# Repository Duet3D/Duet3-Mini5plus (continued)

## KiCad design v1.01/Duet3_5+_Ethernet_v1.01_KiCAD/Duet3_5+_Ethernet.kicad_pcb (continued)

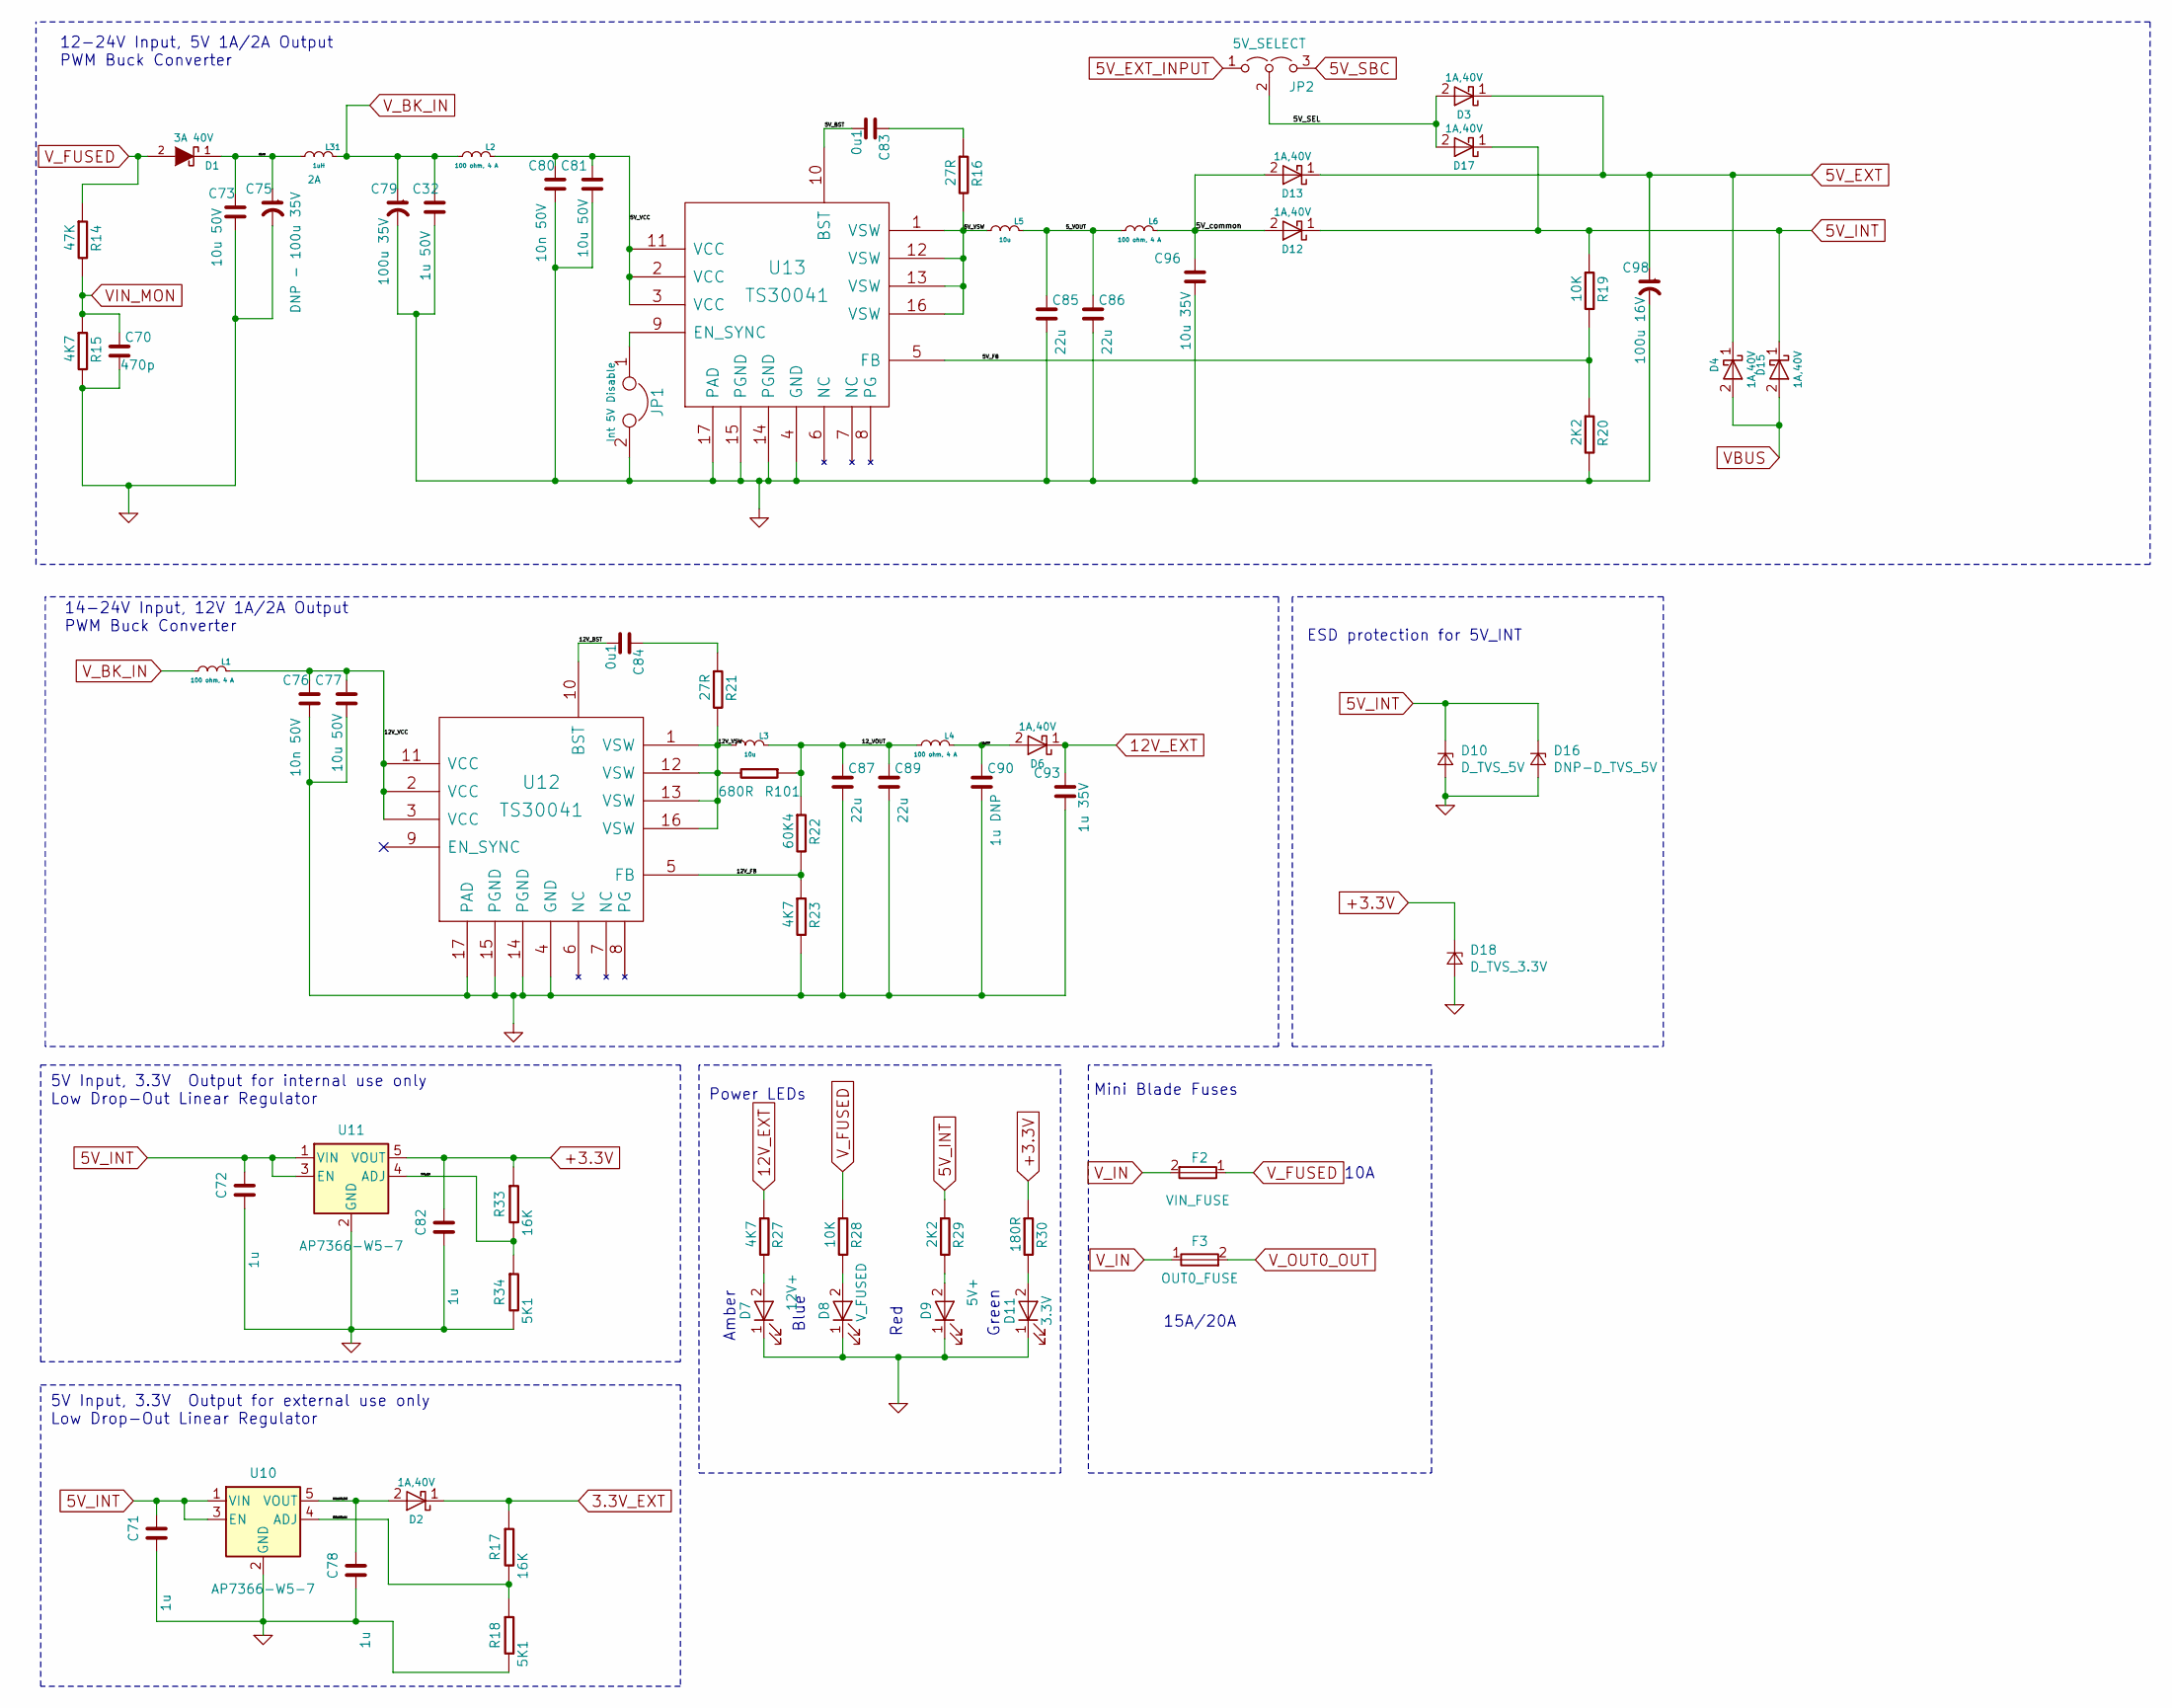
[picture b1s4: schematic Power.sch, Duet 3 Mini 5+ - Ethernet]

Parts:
C32: 1u 50V; C_0603_1608Metric_Wbry; Part Number CL10A105KB8NNNC
C70: 470p; C_0402_1005Metric_Wbry; Part Number CC0402KRX7R9BB471 or similar 10V+
C71, C72, C78, C82: 1u; C_0603_1608Metric_Wbry; Part Number CL10B105MO8NNWC or equivalent 16V+
C73, C77, C81: 10u 50V; C_1206_3216Metric; Part Number CL31A106MBHNNNE
C75: DNP - 100u 35V; CP_Elec_6.3x7.7; Part Number DNP e.g EEEFT1V101AP or 865080545012
C76: 10n 50V; C_0603_1608Metric_Wbry; Part Number CL10B103KB8NNNC
C79: 100u 35V; CP_Elec_6.3x7.7; Part Number e.g EEEFT1V101AP or 865080545012
C80: 10n 50V; C_0603_1608Metric_Wbry; Part Number CL10B103KB8NNNC or similar
C83, C84: 0u1; C_0402_1005Metric_Wbry; Part Number CL05A104KA5NNNC or similar
C85, C86, C87, C89: 22u; C_0805_2012Metric; Rating 25V; Part Number GRM21BR61E226ME44L
C90: 1u DNP; C_0603_1608Metric_Wbry; Rating 35V + DNP; Part Number CL10A105KB8NNNC or equivalent
C93: 1u 35V; C_0603_1608Metric_Wbry; Rating 35V +; Part Number CL10A105KB8NNNC or equivalent 35V+
C96: 10u 35V; C_1206_3216Metric; Part Number CL31A106KBHNNNE or similar 35V+
C98: 100u 16V; CP_Elec_6.3x7.7; Part Number 865080545012 or similar 16V+
D1: 3A 40V; D_SMA; Part Number ACDBA340-HF, SK34ATR or similar
D2, D3, D4, D6, D12, D13, D15, D17: 1A,40V; D_SOD-123F; Rating 1A,40V; Part Number DSS14UTR or RB162MM-40TR or similar
D7: 12V+; LED_0603_1608Metric; Part Number 150060AS75000 or equivalent Amber
D8: V_FUSED; LED_0603_1608Metric; Part Number 150060BS75000 or equivalent Blue
D9: 5V+; LED_0603_1608Metric; Part Number 150060RS75000 or equivalent Red
D10: D_TVS_5V; DFN1610-2L; Part Number 824032815 or 824031815 (DNP if D16 is p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
D11: 3.3V; LED_0603_1608Metric; Part Number 150060VS75000 or equivalent Green
D16: DNP-D_TVS_5V; D_SMC; Part Number SMCJ5.0A (DNP if D10 is populated)
D18: D_TVS_3.3V; DFN1610-2L; Part Number 824032813
F2: VIN_FUSE; MCCQ-122-minibladefuseholder; Part Number MCCQ-122 + 10A fuse
F3: OUT0_FUSE; MCCQ-122-minibladefuseholder; Part Number MCCQ-122 +15A fuse
JP1: Int 5V Disable; PinHeader_1x02_P2.54mm_Vertical; Part Number THS-02-R
JP2: 5V_SELECT; PinHeader_1x03_P2.54mm_Vertical; Part Number THS-03-R
L1, L2, L4, L6: 100 ohm, 4 A; L_0805_2012Metric; Part Number MPZ2012S101A or similar
L3, L5: 10u; L_Wuerth_7440405xxxx; Part Number 74404054100 or NR5040T100M
L31: 1uH; L_0806_2016Metric; Rating 2A; Part Number BDCD002016101R0MS1 or MAKK2016T1R0M
R14: 47K; R_0402_1005Metric_Wbry; Part Number RMCF0402FT47K0
R15, R23, R27: 4K7; R_0402_1005Metric_Wbry; Part Number RK73H1ETTP4701F
R16, R21: 27R; R_0402_1005Metric_Wbry; Rating 0.1W+; Part Number RK73H1ETTP10R0F
R17, R33: 16K; R_0402_1005Metric_Wbry; Part Number RMCF0402FT16K0
R18, R34: 5K1; R_0402_1005Metric_Wbry; Part Number ERJ3EKF5101V
R19, R28: 10K; R_0402_1005Metric_Wbry; Part Number RK73H1ETTP1002F
R20, R29: 2K2; R_0402_1005Metric_Wbry; Part Number RK73H1ETTP2201F
R22: 60K4; R_0402_1005Metric_Wbry; Part Number ERJ-2RKF6042X
R30: 180R; R_0402_1005Metric_Wbry; Part Number RMCF0402FT180R
R101: 680R; R_0805_2012Metric; Rating 0.5W; Part Number 680R 0.5W (ERJ-P06F6653V 665R is an alt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
U10, U11: AP7366-W5-7; SOT-23-5; Part Number AP7366-W5-7
U12, U13: TS30041; QFN-16-1EP_3x3mm_P0.5mm_EP1.8x1.8mm_ThermalVias; Part Number TS30041-M000QFNR

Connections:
3.3V_EXT: D2.1 (K), R17.1; also elsewhere on the board
5V_EXT: C98.1, D3.1 (K), D4.1 (K), D13.1 (K); also elsewhere on the board
5V_EXT_INPUT: JP2.1 (A); also elsewhere on the board
5V_INT: C71.1, C72.1, D10.1 (K), D12.1 (K), D15.1 (K), D16.1 (K), D17.1 (K), R19.1, R29.1, U10.1 (VIN), U10.3 (EN), U11.1 (VIN), U11.3 (EN); also elsewhere on the board
5V_SBC: JP2.3 (B); also elsewhere on the board
12V_EXT: C93.1, D6.1 (K), R27.1; also elsewhere on the board
+3.3V: C82.1, D18.1 (K), R30.1, R33.1, U11.5 (VOUT); also elsewhere on the board
/Power/3V3_ADJ: R33.2, R34.1, U11.4 (ADJ)
/Power/3V3_EXT_ADJ: R17.2, R18.1, U10.4 (ADJ)
/Power/3V3_EXT_OUT: C78.1, D2.2 (A), U10.5 (VOUT)
/Power/5V_BST: C83.2, U13.10 (BST)
/Power/5V_FB: R19.2, R20.1, U13.5 (FB)
/Power/5V_SEL: D3.2 (A), D17.2 (A), JP2.2 (C)
/Power/5V_VCC: C80.1, C81.1, L2.1 (A), U13.2 (VCC), U13.3 (VCC), U13.11 (VCC)
/Power/5V_VSW: L5.2 (B), R16.2, U13.1 (VSW), U13.12 (VSW), U13.13 (VSW), U13.16 (VSW)
/Power/5V_common: C96.1, D12.2 (A), D13.2 (A), L6.1 (A)
/Power/5_VOUT: C85.1, C86.1, L5.1 (A), L6.2 (B)
/Power/12V_BST: C84.2, U12.10 (BST)
/Power/12V_FB: R22.2, R23.1, U12.5 (FB)
/Power/12V_VCC: C76.1, C77.1, L1.1 (A), U12.2 (VCC), U12.3 (VCC), U12.11 (VCC)
/Power/12V_VSW: L3.2 (B), R21.2, R101.2, U12.1 (VSW), U12.12 (VSW), U12.13 (VSW), U12.16 (VSW)
/Power/12_VOUT: C87.1, C89.1, L3.1 (A), L4.2 (B), R22.1, R101.1
/Power/L4_OUT: C90.1, D6.2 (A), L4.1 (A)
/Power/d1out: C73.1, C75.1, D1.1 (K), L31.2 (B)
GND: C32.2, C70.2, C71.2, C72.2, C73.2, C75.2, C76.2, C77.2, C78.2, C79.2, C80.2, C81.2, C82.2, C85.2, C86.2, C87.2, C89.2, C90.2, C93.2, C96.2, C98.2, D7.1 (K), D8.1 (K), D9.1 (K), D10.2 (A), D11.1 (K), D16.2 (A), D18.2 (A), JP1.2, R15.2, R18.2, R20.2, R23.2, R34.2, U10.2 (GND), U11.2 (GND), U12.4 (GND), U12.14 (PGND), U12.15 (PGND), U12.17 (PAD), U13.4 (GND), U13.14 (PGND), U13.15 (PGND), U13.17 (PAD); also elsewhere on the board
unnamed: C83.1, R16.1
unnamed: C84.1, R21.1
unnamed: D7.2 (A), R27.2
unnamed: D8.2 (A), R28.2
unnamed: D9.2 (A), R29.2
unnamed: D11.2 (A), R30.2
unnamed: JP1.1, U13.9 (EN_SYNC)
VBUS: D4.2 (A), D15.2 (A); also elsewhere on the board
VIN_MON: C70.1, R14.2, R15.1; also elsewhere on the board
V_BK_IN: C32.1, C79.1, L1.2 (B), L2.2 (B), L31.1 (A)
V_FUSED: D1.2 (A), F2.1, R14.1, R28.1; also elsewhere on the board
V_IN: F2.2, F3.1; also elsewhere on the board
V_OUT0_OUT: F3.2; also elsewhere on the board

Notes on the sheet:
Mini Blade Fuses
5V Input, 3.3V Output for internal use only Low Drop-Out Linear Regulator
Power LEDs
Blue
Red
Green
10A
15A/20A
5V Input, 3.3V Output for external use only Low Drop-Out Linear Regulator
14-24V Input, 12V 1A/2A Output PWM Buck Converter
Amber
ESD protection for 5V_INT
12-24V Input, 5V 1A/2A Output PWM Buck Converter

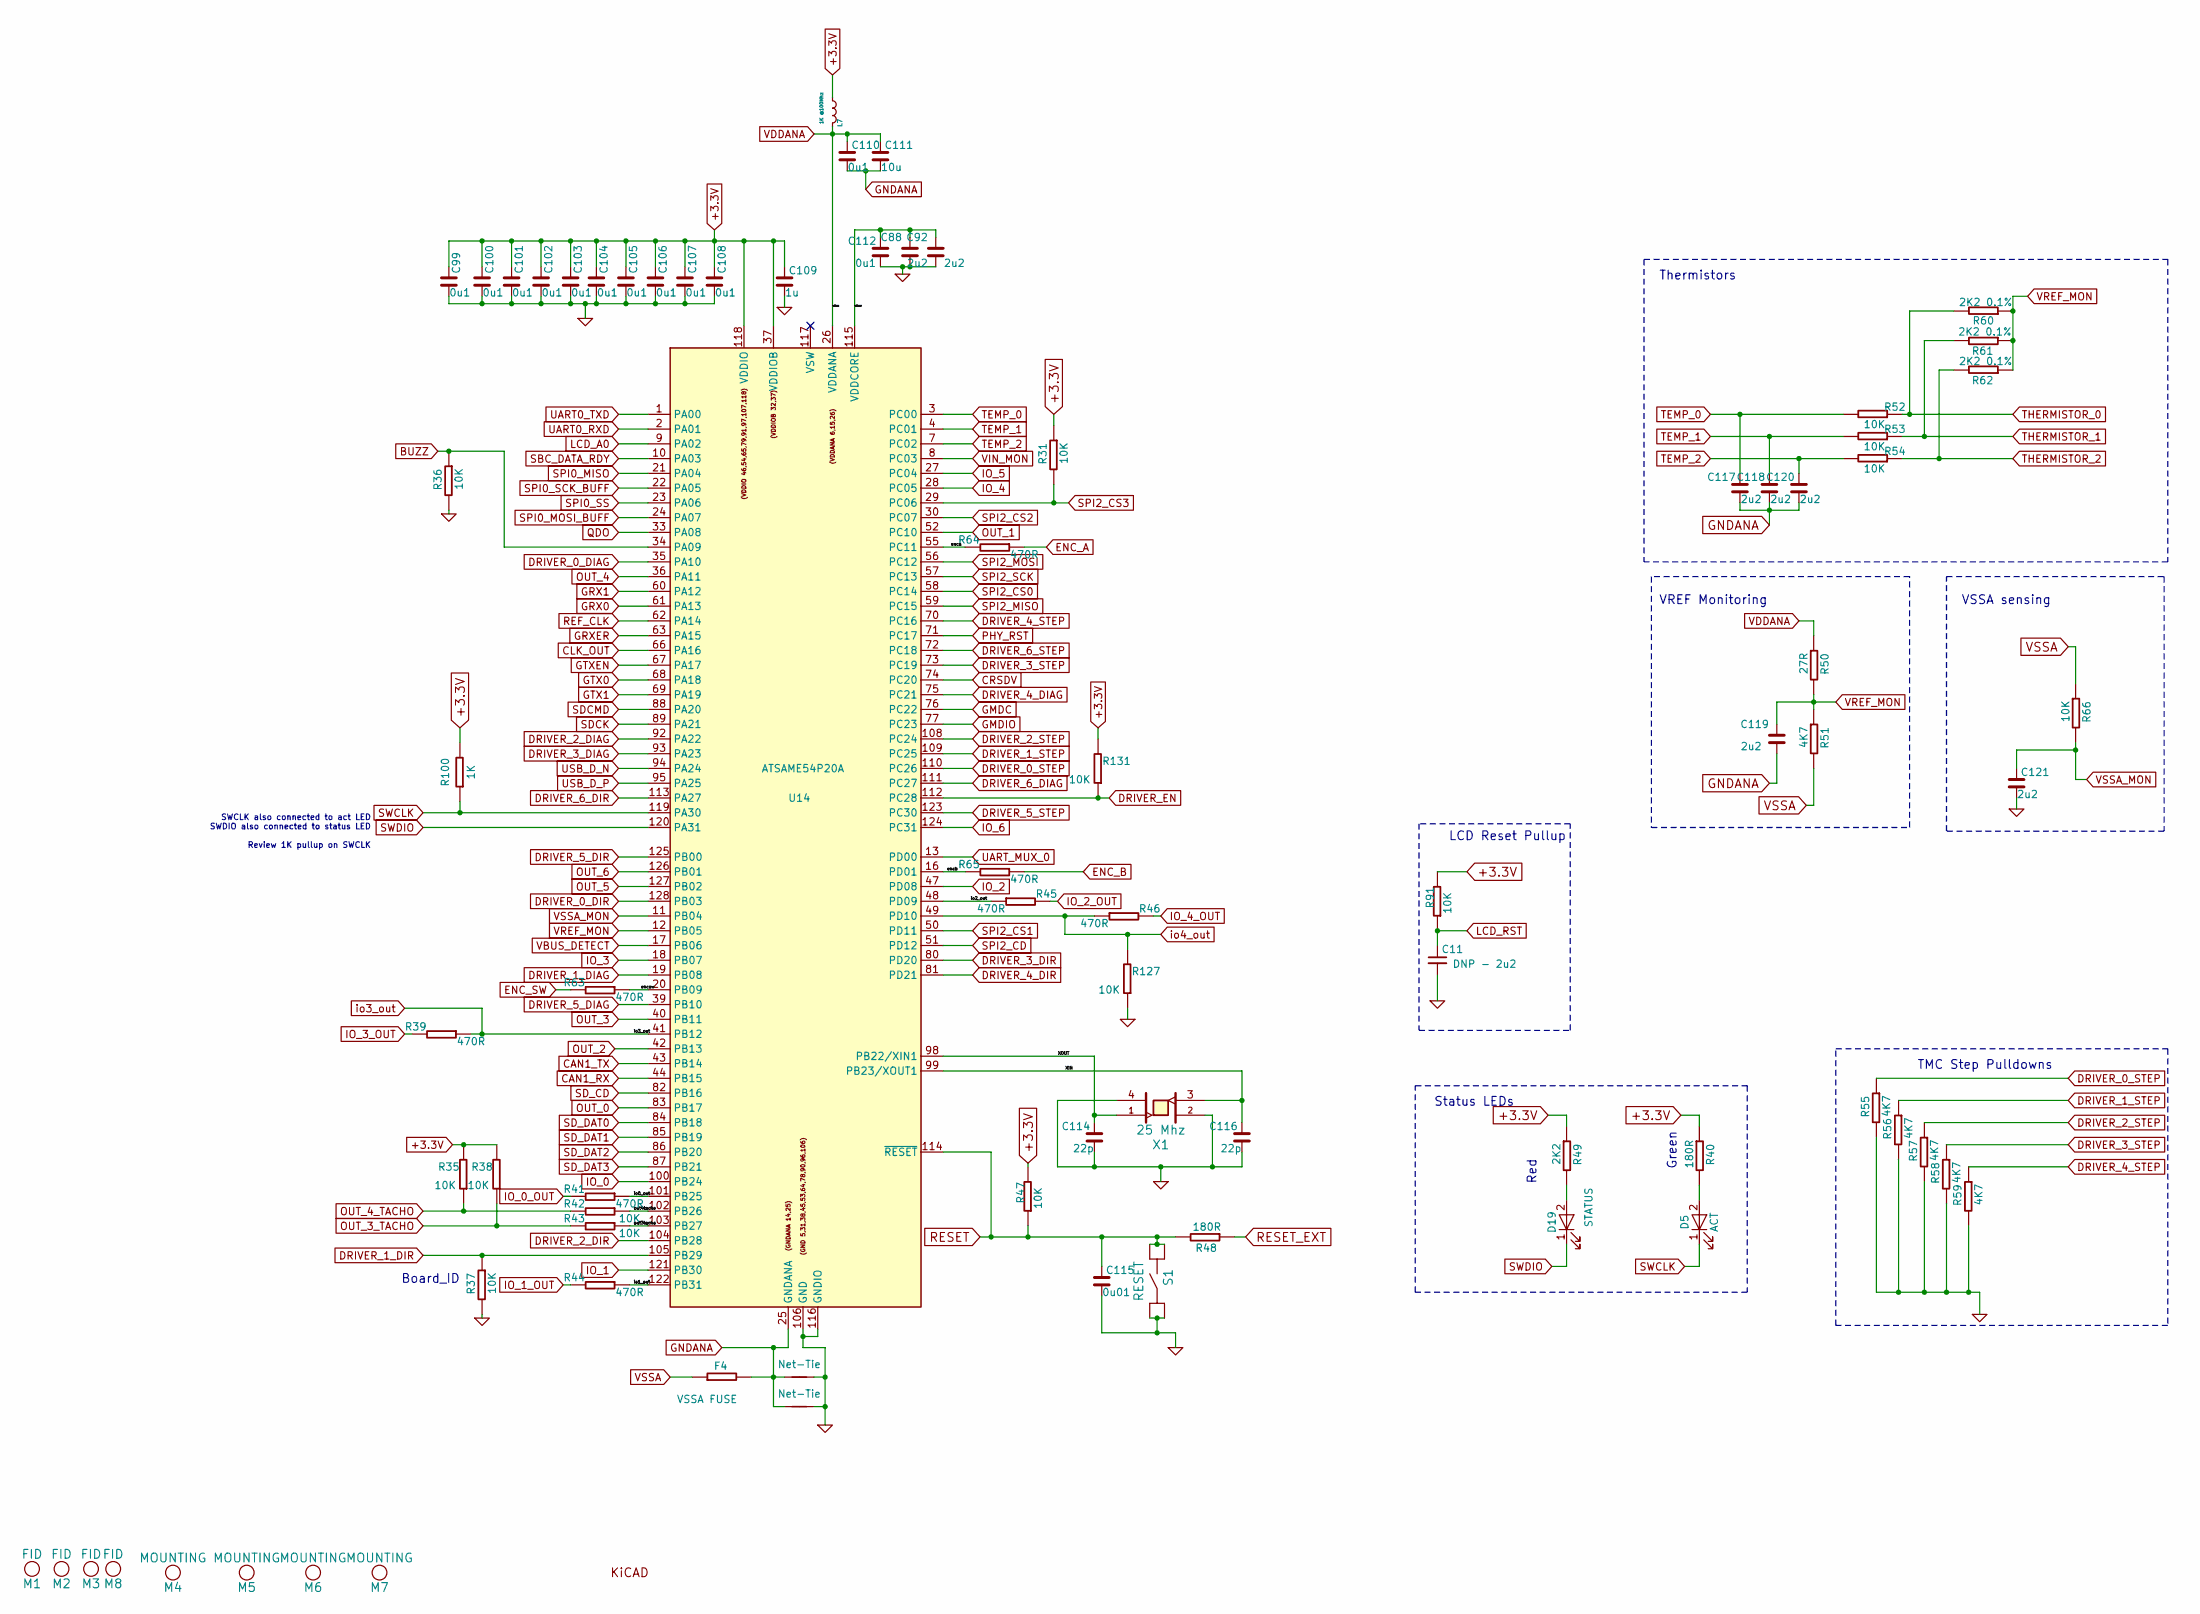
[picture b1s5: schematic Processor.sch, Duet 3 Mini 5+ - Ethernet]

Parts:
C11: DNP - 2u2; C_0402_1005Metric_Wbry; Part Number DNP - LMK105BJ225KV-F or similar 10v+
C88, C92, C117, C118, C119, C120, C121: 2u2; C_0402_1005Metric_Wbry; Part Number LMK105BJ225KV-F or similar 10v+
C99, C100, C101, C102, C103, C104, C105, C106, C107, C108, C110, C112: 0u1; C_0402_1005Metric_Wbry; Part Number CL05A104KA5NNNC or similar
C109: 1u; C_0603_1608Metric_Wbry; Part Number CL10B105MO8NNWC or equivalent 16V+
C111: 10u; C_0805_2012Metric; Part Number e.g CL21A106KQCLRNC
C114, C116: 22p; C_0402_1005Metric_Wbry; Part Number C0402C220J4GACTU
C115: 0u01; C_0402_1005Metric_Wbry; Part Number TMK105B7103KV-F
D5: ACT; LED_0603_1608Metric; Part Number 150060VS75000 or equivalent Green
D19: STATUS; LED_0603_1608Metric; Part Number 150060RS75000 or equivalent Red
F4: VSSA FUSE; Fuse_1206_3216Metric; Part Number 0ZCJ0020FF2E
L7: 1K @100Mhz; L_0603_1608Metric; Part Number BK1608HS102-T or PE-0603FB102ST or simi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
M1, M2, M3, M8: FID; Fiducial_1mm_Mask2mm; Part Number DNP - Virtual component
M4, M5, M6, M7: MOUNTING; MountingHole_4.3mm_M4; Part Number DNP - Virtual component
M12: Logo_KICAD; KiCad-Logo_6mm_SilkScreen; Part Number DNP - Virtual component
NT1, NT2: Net-Tie; NetTie-2_SMD_Pad0.5mm; Part Number DNP - Virtual component
R31, R35, R36, R37, R38, R42, R43, R47, R52, R53, R54, R66, R91, R127, R131: 10K; R_0402_1005Metric_Wbry; Part Number RK73H1ETTP1002F
R39, R41, R44, R45, R46, R63, R64, R65: 470R; R_0402_1005Metric_Wbry; Part Number RK73H1ETTP4700F
R40, R48: 180R; R_0402_1005Metric_Wbry; Part Number RMCF0402FT180R
R49: 2K2; R_0402_1005Metric_Wbry; Part Number RK73H1ETTP2201F
R50: 27R; R_0402_1005Metric_Wbry; Part Number RC0402FR-0727RL
R51, R55, R56, R57, R58, R59: 4K7; R_0402_1005Metric_Wbry; Part Number RK73H1ETTP4701F
R60, R61, R62: 2K2 0.1%; R_0402_1005Metric_Wbry; Part Number RT0402BRE072K2L
R100: 1K; R_0402_1005Metric_Wbry; Part Number RK73H1ETTP1001F
S1: RESET; SW_SIDE_1_lugs; Part Number LY-A03-02A
U14: ATSAME54P20A; TQFP-128_14x14mm_P0.4mm; Part Number ATSAME54P20A
X1: TSX-3225 25.0000MF10P; Crystal_SMD_ECS-33B-4Pin_3.2x2.5mm; Part Number TSX-3225 25.0000MF10P

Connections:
+3.3V: C99.1, C100.1, C101.1, C102.1, C103.1, C104.1, C105.1, C106.1, C107.1, C108.1, C109.1, L7.2 (B), R31.1, R35.2, R38.2, R40.1, R47.2, R49.1, R91.2, R100.2, R131.2, U14.32 (VDDIOB), U14.37 (VDDIOB), U14.46 (VDDIO), U14.54 (VDDIO), U14.65 (VDDIO), U14.79 (VDDIO), U14.91 (VDDIO), U14.97 (VDDIO), U14.107 (VDDIO), U14.118 (VDDIO); also elsewhere on the board
/Processor/XIN: C116.1, U14.99 (PB23/XOUT1), X1.3
/Processor/XOUT: C114.1, U14.98 (PB22/XIN1), X1.1
/Processor/enca: R64.2, U14.55 (PC11)
/Processor/encb: R65.2, U14.16 (PD01)
/Processor/encsw: R63.1, U14.20 (PB09)
/Processor/io0_out: R41.1, U14.101 (PB25)
/Processor/io1_out: R44.1, U14.122 (PB31)
/Processor/io2_out: R45.1, U14.48 (PD09)
/Processor/out3tacho: R43.1, U14.103 (PB27)
/Processor/out4tacho: R42.1, U14.102 (PB26)
/Processor/vddcore: C88.1, C92.1, C112.1, U14.115 (VDDCORE)
BUZZ: R36.1, U14.34 (PA09); also elsewhere on the board
CAN1_RX: U14.44 (PB15); also elsewhere on the board
CAN1_TX: U14.43 (PB14); also elsewhere on the board
CLK_OUT: U14.66 (PA16); also elsewhere on the board
CRSDV: U14.74 (PC20); also elsewhere on the board
DRIVER_0_DIAG: U14.35 (PA10); also elsewhere on the board
DRIVER_0_DIR: U14.128 (PB03); also elsewhere on the board
DRIVER_0_STEP: R55.1, U14.110 (PC26); also elsewhere on the board
DRIVER_1_DIAG: U14.19 (PB08); also elsewhere on the board
DRIVER_1_DIR: R37.1, U14.105 (PB29); also elsewhere on the board
DRIVER_1_STEP: R56.1, U14.109 (PC25); also elsewhere on the board
DRIVER_2_DIAG: U14.92 (PA22); also elsewhere on the board
DRIVER_2_DIR: U14.104 (PB28); also elsewhere on the board
DRIVER_2_STEP: R57.1, U14.108 (PC24); also elsewhere on the board
DRIVER_3_DIAG: U14.93 (PA23); also elsewhere on the board
DRIVER_3_DIR: U14.80 (PD20); also elsewhere on the board
DRIVER_3_STEP: R58.1, U14.73 (PC19); also elsewhere on the board
DRIVER_4_DIAG: U14.75 (PC21); also elsewhere on the board
DRIVER_4_DIR: U14.81 (PD21); also elsewhere on the board
DRIVER_4_STEP: R59.1, U14.70 (PC16); also elsewhere on the board
DRIVER_5_DIAG: U14.39 (PB10); also elsewhere on the board
DRIVER_5_DIR: U14.125 (PB00); also elsewhere on the board
DRIVER_5_STEP: U14.123 (PC30); also elsewhere on the board
DRIVER_6_DIAG: U14.111 (PC27); also elsewhere on the board
DRIVER_6_DIR: U14.113 (PA27); also elsewhere on the board
DRIVER_6_STEP: U14.72 (PC18); also elsewhere on the board
DRIVER_EN: R131.1, U14.112 (PC28); also elsewhere on the board
ENC_A: R64.1; also elsewhere on the board
ENC_B: R65.1; also elsewhere on the board
ENC_SW: R63.2; also elsewhere on the board
GMDC: U14.76 (PC22); also elsewhere on the board
GMDIO: U14.77 (PC23); also elsewhere on the board
GND: C11.2, C88.2, C92.2, C99.2, C100.2, C101.2, C102.2, C103.2, C104.2, C105.2, C106.2, C107.2, C108.2, C109.2, C112.2, C114.2, C115.2, C116.2, C121.2, NT1.2, NT2.2, R36.2, R37.2, R55.2, R56.2, R57.2, R58.2, R59.2, R127.1, S1.1, S1.2, U14.5 (GND), U14.31 (GND), U14.38 (GND), U14.45 (GND), U14.53 (GND), U14.64 (GND), U14.78 (GND), U14.90 (GND), U14.96 (GND), U14.106 (GND), U14.116 (GNDIO), X1.2, X1.4; also elsewhere on the board
GNDANA: C110.2, C111.2, C117.2, C118.2, C119.2, C120.2, F4.2, NT1.1, NT2.1, U14.14 (GNDANA), U14.25 (GNDANA)
GRX0: U14.61 (PA13); also elsewhere on the board
GRX1: U14.60 (PA12); also elsewhere on the board
GRXER: U14.63 (PA15); also elsewhere on the board
GTX0: U14.68 (PA18); also elsewhere on the board
GTX1: U14.69 (PA19); also elsewhere on the board
GTXEN: U14.67 (PA17); also elsewhere on the board
IO_0: U14.100 (PB24); also elsewhere on the board
IO_0_OUT: R41.2; also elsewhere on the board
IO_1: U14.121 (PB30); also elsewhere on the board
IO_1_OUT: R44.2; also elsewhere on the board
IO_2: U14.47 (PD08); also elsewhere on the board
IO_2_OUT: R45.2; also elsewhere on the board
IO_3: U14.18 (PB07); also elsewhere on the board
IO_3_OUT: R39.2; also elsewhere on the board
IO_4: U14.28 (PC05); also elsewhere on the board
IO_4_OUT: R46.2; also elsewhere on the board
IO_5: U14.27 (PC04); also elsewhere on the board
IO_6: U14.124 (PC31); also elsewhere on the board
LCD_A0: U14.9 (PA02); also elsewhere on the board
LCD_RST: C11.1, R91.1; also elsewhere on the board
unnamed: D5.2 (A), R40.2
unnamed: D19.2 (A), R49.2
OUT_0: U14.83 (PB17); also elsewhere on the board
OUT_1: U14.52 (PC10); also elsewhere on the board
OUT_2: U14.42 (PB13); also elsewhere on the board
OUT_3: U14.40 (PB11); also elsewhere on the board
OUT_3_TACHO: R38.1, R43.2; also elsewhere on the board
OUT_4: U14.36 (PA11); also elsewhere on the board
OUT_4_TACHO: R35.1, R42.2; also elsewhere on the board
OUT_5: U14.127 (PB02); also elsewhere on the board
OUT_6: U14.126 (PB01); also elsewhere on the board
PHY_RST: U14.71 (PC17); also elsewhere on the board
QDO: U14.33 (PA08); also elsewhere on the board
REF_CLK: U14.62 (PA14); also elsewhere on the board
RESET: C115.1, R47.1, R48.2, S1.3, S1.4, U14.114 (~RESET); also elsewhere on the board
RESET_EXT: R48.1; also elsewhere on the board
SBC_DATA_RDY: U14.10 (PA03); also elsewhere on the board
SDCK: U14.89 (PA21); also elsewhere on the board
SDCMD: U14.88 (PA20); also elsewhere on the board
SD_CD: U14.82 (PB16); also elsewhere on the board
SD_DAT0: U14.84 (PB18); also elsewhere on the board
SD_DAT1: U14.85 (PB19); also elsewhere on the board
SD_DAT2: U14.86 (PB20); also elsewhere on the board
SD_DAT3: U14.87 (PB21); also elsewhere on the board
SPI0_MISO: U14.21 (PA04); also elsewhere on the board
SPI0_MOSI_BUFF: U14.24 (PA07); also elsewhere on the board
SPI0_SCK_BUFF: U14.22 (PA05); also elsewhere on the board
SPI0_SS: U14.23 (PA06); also elsewhere on the board
SPI2_CD: U14.51 (PD12); also elsewhere on the board
SPI2_CS0: U14.58 (PC14); also elsewhere on the board
SPI2_CS1: U14.50 (PD11); also elsewhere on the board
SPI2_CS2: U14.30 (PC07); also elsewhere on the board
SPI2_CS3: R31.2, U14.29 (PC06); also elsewhere on the board
SPI2_MISO: U14.59 (PC15); also elsewhere on the board
SPI2_MOSI: U14.56 (PC12); also elsewhere on the board
SPI2_SCK: U14.57 (PC13); also elsewhere on the board
SWCLK: D5.1 (K), R100.1, U14.119 (PA30); also elsewhere on the board
SWDIO: D19.1 (K), U14.120 (PA31); also elsewhere on the board
TEMP_0: C117.1, R52.2, U14.3 (PC00)
TEMP_1: C118.1, R53.2, U14.4 (PC01)
TEMP_2: C120.1, R54.2, U14.7 (PC02)
THERMISTOR_0: R52.1, R60.2; also elsewhere on the board
THERMISTOR_1: R53.1, R61.2; also elsewhere on the board
THERMISTOR_2: R54.1, R62.2; also elsewhere on the board
UART0_RXD: U14.2 (PA01); also elsewhere on the board
UART0_TXD: U14.1 (PA00); also elsewhere on the board
UART_MUX_0: U14.13 (PD00); also elsewhere on the board
USB_D_N: U14.94 (PA24); also elsewhere on the board
USB_D_P: U14.95 (PA25); also elsewhere on the board
VBUS_DETECT: U14.17 (PB06); also elsewhere on the board
VDDANA: C110.1, C111.1, L7.1 (A), R50.1, U14.6 (VDDANA), U14.15 (VDDANA), U14.26 (VDDANA)
VIN_MON: U14.8 (PC03); also elsewhere on the board
VREF_MON: C119.1, R50.2, R51.1, R60.1, R61.1, R62.1, U14.12 (PB05)
VSSA: F4.1, R51.2, R66.1; also elsewhere on the board
VSSA_MON: C121.1, R66.2, U14.11 (PB04)
io3_out: R39.1, U14.41 (PB12); also elsewhere on the board
io4_out: R46.1, R127.2, U14.49 (PD10); also elsewhere on the board

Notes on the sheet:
VSSA sensing
Red
Status LEDs
TMC Step Pulldowns
Thermistors
VREF Monitoring
SWCLK also connected to act LED SWDIO also connected to status LED Review 1K pullup on SWCLK
Board_ID
LCD Reset Pullup
Green

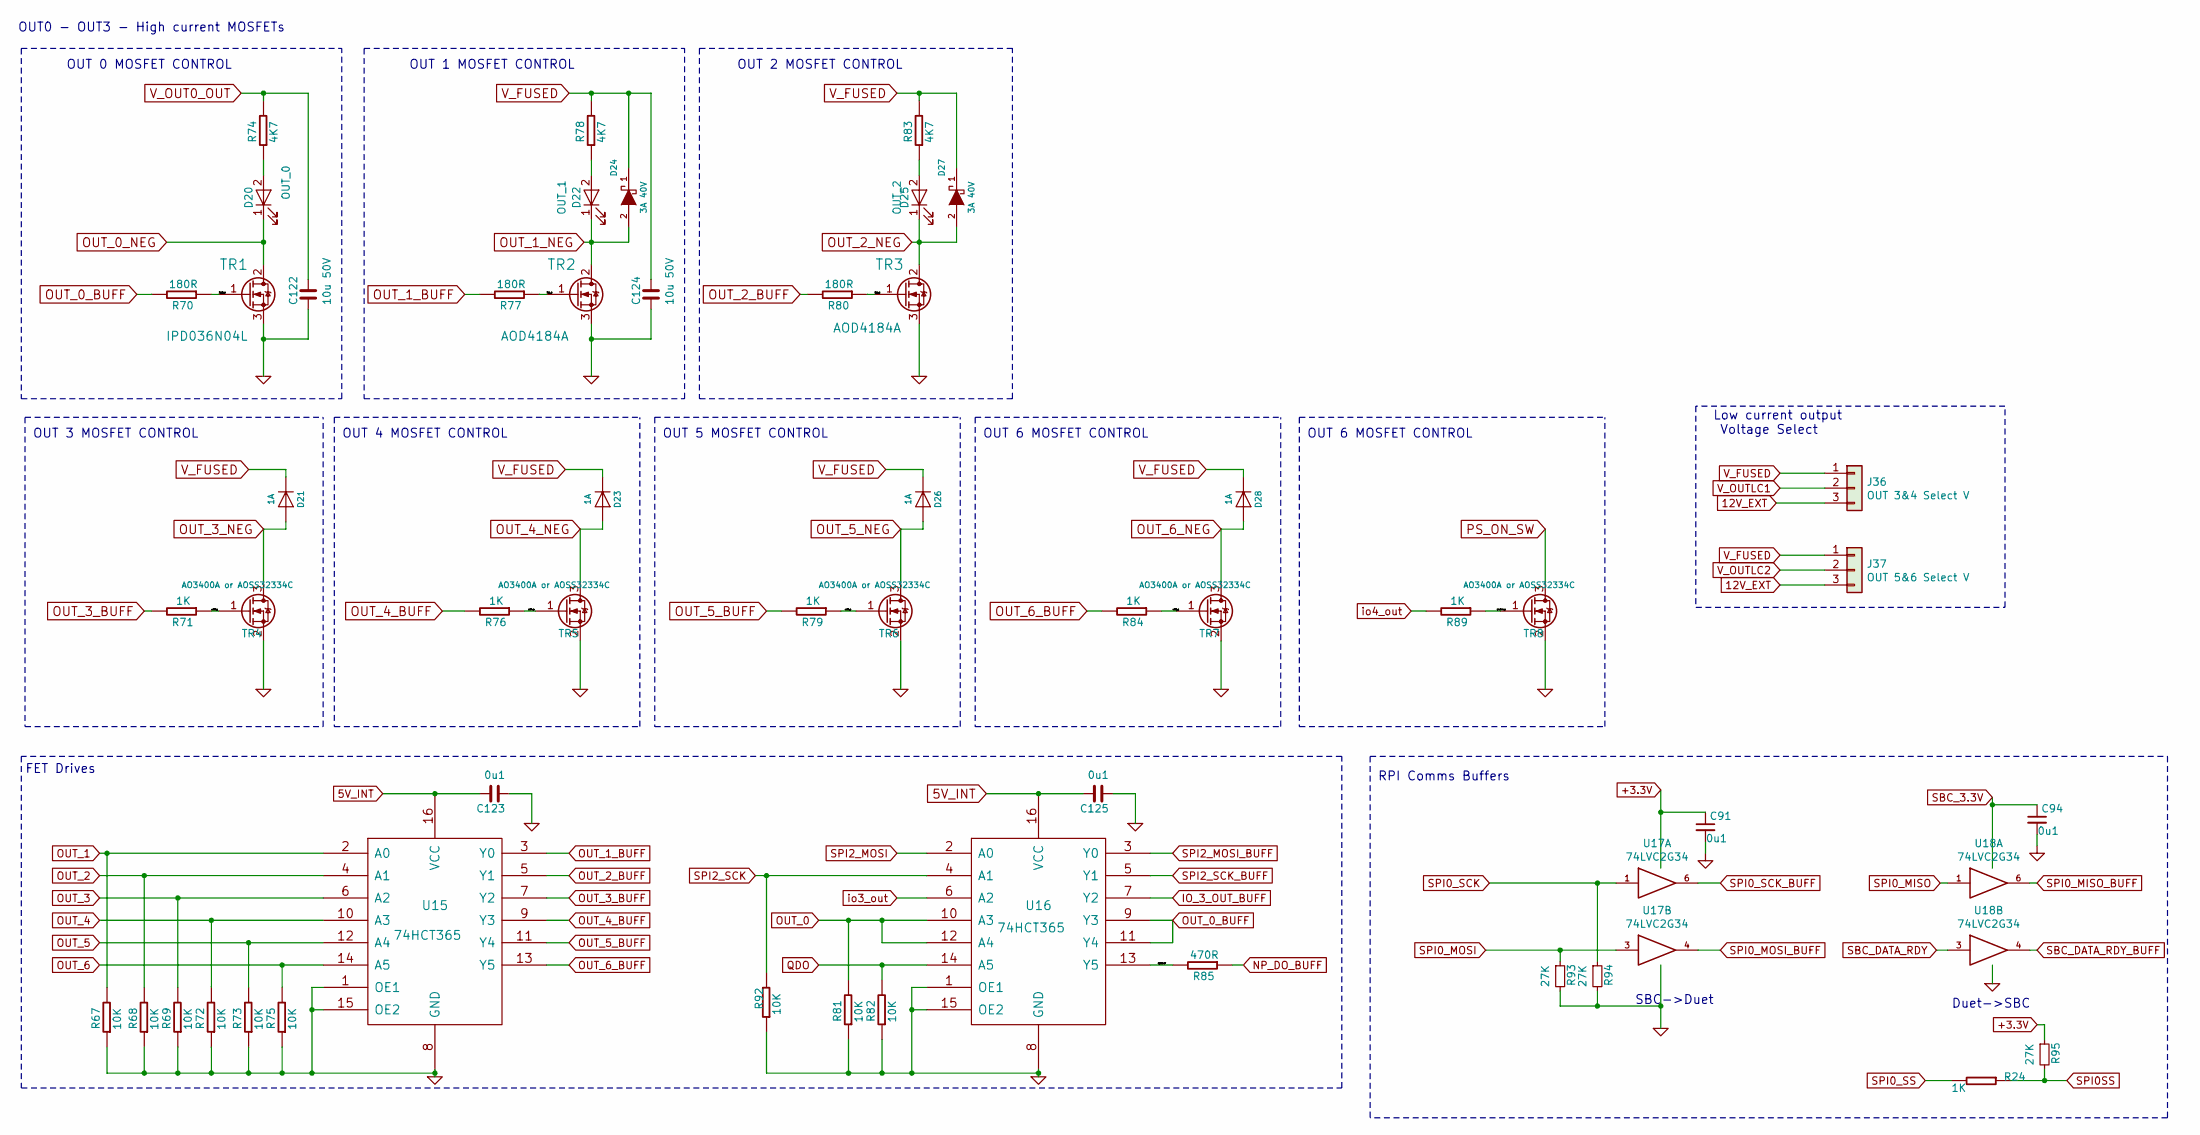
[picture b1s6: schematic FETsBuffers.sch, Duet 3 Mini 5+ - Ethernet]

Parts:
C91, C94, C123, C125: 0u1; C_0402_1005Metric_Wbry; Part Number CL05A104KA5NNNC or similar
C122, C124: 10u 50V; C_1206_3216Metric; Part Number CL31A106MBHNNNE
D20: OUT_0; LED_0603_1608Metric; Part Number 150060RS75000 or equivalent Red
D21, D23, D26, D28: 1A; D_SOD-123F; Part Number HS1KFL or equivalent
D22: OUT_1; LED_0603_1608Metric; Part Number 150060RS75000 or equivalent Red
D24, D27: 3A 40V; D_SMA; Part Number ACDBA340-HF, SK34ATR or similar
D25: OUT_2; LED_0603_1608Metric; Part Number 150060RS75000 or equivalent Red
J36: OUT 3&4 Select V; PinHeader_1x03_P2.54mm_Vertical; Part Number THS-03-R
J37: OUT 5&6 Select V; PinHeader_1x03_P2.54mm_Vertical; Part Number THS-03-RT
R24, R71, R76, R79, R84, R89: 1K; R_0402_1005Metric_Wbry; Part Number RK73H1ETTP1001F
R67, R68, R69, R72, R73, R75, R81, R82, R92: 10K; R_0402_1005Metric_Wbry; Part Number RK73H1ETTP1002F
R70, R77, R80: 180R; R_0402_1005Metric_Wbry; Part Number RMCF0402FT180R
R74, R78, R83: 4K7; R_0402_1005Metric_Wbry; Part Number RK73H1ETTP4701F
R85: 470R; R_0402_1005Metric_Wbry; Part Number RK73H1ETTP4700F
R93, R94, R95: 27K; R_0402_1005Metric_Wbry; Part Number RK73H1ETTP2702F
TR1: IPD036N04L; TO-252-2_vias; Part Number IPD90N04S4L04ATMA1
TR2, TR3: AOD4184A; TO-252-2_vias; Part Number AOD4184A
TR4, TR5, TR6, TR7, TR8: AO3400A; SOT-23_AO3400A; Part Number AO3400A or AOSS32334C
U15, U16: 74HCT365; TSSOP-16_4.4x5mm_P0.65mm; Part Number MC74HCT365ADTR2G or equivalent
U17, U18: 74LVC2G34; SOT-363_SC-70-6; Part Number 74LVC2G34GW,125

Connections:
5V_INT: C123.1, C125.1, U15.16 (VCC), U16.16 (VCC); also elsewhere on the board
12V_EXT: J36.3, J37.3; also elsewhere on the board
+3.3V: C91.1, R95.1, U17.5; also elsewhere on the board
/MOSFETs and Buffers/TR1_G: R77.1, TR2.1 (G)
/MOSFETs and Buffers/TR3_G: R80.1, TR3.1 (G)
/MOSFETs and Buffers/TR10_G: R70.1, TR1.1 (G)
/MOSFETs and Buffers/npdobuff: R85.2, U16.13 (Y5)
/MOSFETs and Buffers/out3_g: R71.1, TR4.1 (G)
/MOSFETs and Buffers/out4_g: R76.1, TR5.1 (G)
/MOSFETs and Buffers/out5_g: R79.1, TR6.1 (G)
/MOSFETs and Buffers/out6_g: R84.1, TR7.1 (G)
/MOSFETs and Buffers/psonsw_g: R89.1, TR8.1 (G)
GND: C91.2, C94.2, C122.2, C123.2, C124.2, C125.2, R67.1, R68.1, R69.1, R72.1, R73.1, R75.1, R81.1, R82.1, R92.1, R93.2, R94.2, TR1.3 (S), TR2.3 (S), TR3.3 (S), TR4.2 (S), TR5.2 (S), TR6.2 (S), TR7.2 (S), TR8.2 (S), U15.1 (OE1), U15.8 (GND), U15.15 (OE2), U16.1 (OE1), U16.8 (GND), U16.15 (OE2), U17.2 (GND), U18.2 (GND); also elsewhere on the board
IO_3_OUT_BUFF: U16.7 (Y2); also elsewhere on the board
NP_DO_BUFF: R85.1; also elsewhere on the board
unnamed: D20.2 (A), R74.1
unnamed: D22.2 (A), R78.1
unnamed: D25.2 (A), R83.1
OUT_0: R81.2, U16.10 (A3), U16.12 (A4); also elsewhere on the board
OUT_0_BUFF: R70.2, U16.9 (Y3), U16.11 (Y4)
OUT_0_NEG: D20.1 (K), TR1.2 (D); also elsewhere on the board
OUT_1: R67.2, U15.2 (A0); also elsewhere on the board
OUT_1_BUFF: R77.2, U15.3 (Y0)
OUT_1_NEG: D22.1 (K), D24.2 (A), TR2.2 (D); also elsewhere on the board
OUT_2: R68.2, U15.4 (A1); also elsewhere on the board
OUT_2_BUFF: R80.2, U15.5 (Y1)
OUT_2_NEG: D25.1 (K), D27.2 (A), TR3.2 (D); also elsewhere on the board
OUT_3: R69.2, U15.6 (A2); also elsewhere on the board
OUT_3_BUFF: R71.2, U15.7 (Y2)
OUT_3_NEG: D21.2 (A), TR4.3 (D); also elsewhere on the board
OUT_4: R72.2, U15.10 (A3); also elsewhere on the board
OUT_4_BUFF: R76.2, U15.9 (Y3)
OUT_4_NEG: D23.2 (A), TR5.3 (D); also elsewhere on the board
OUT_5: R73.2, U15.12 (A4); also elsewhere on the board
OUT_5_BUFF: R79.2, U15.11 (Y4)
OUT_5_NEG: D26.2 (A), TR6.3 (D); also elsewhere on the board
OUT_6: R75.2, U15.14 (A5); also elsewhere on the board
OUT_6_BUFF: R84.2, U15.13 (Y5); also elsewhere on the board
OUT_6_NEG: D28.2 (A), TR7.3 (D); also elsewhere on the board
PS_ON_SW: TR8.3 (D); also elsewhere on the board
QDO: R82.2, U16.14 (A5); also elsewhere on the board
SBC_3.3V: C94.1, U18.5; also elsewhere on the board
SBC_DATA_RDY: U18.3; also elsewhere on the board
SBC_DATA_RDY_BUFF: U18.4; also elsewhere on the board
SPI0SS: R24.1, R95.2; also elsewhere on the board
SPI0_MISO: U18.1; also elsewhere on the board
SPI0_MISO_BUFF: U18.6; also elsewhere on the board
SPI0_MOSI: R93.1, U17.3; also elsewhere on the board
SPI0_MOSI_BUFF: U17.4; also elsewhere on the board
SPI0_SCK: R94.1, U17.1; also elsewhere on the board
SPI0_SCK_BUFF: U17.6; also elsewhere on the board
SPI0_SS: R24.2; also elsewhere on the board
SPI2_MOSI: U16.2 (A0); also elsewhere on the board
SPI2_MOSI_BUFF: U16.3 (Y0); also elsewhere on the board
SPI2_SCK: R92.2, U16.4 (A1); also elsewhere on the board
SPI2_SCK_BUFF: U16.5 (Y1); also elsewhere on the board
V_FUSED: C124.1, D21.1 (K), D23.1 (K), D24.1 (K), D26.1 (K), D27.1 (K), D28.1 (K), J36.1, J37.1, R78.2, R83.2; also elsewhere on the board
V_OUT0_OUT: C122.1, R74.2; also elsewhere on the board
V_OUTLC1: J36.2; also elsewhere on the board
V_OUTLC2: J37.2; also elsewhere on the board
io3_out: U16.6 (A2); also elsewhere on the board
io4_out: R89.2; also elsewhere on the board

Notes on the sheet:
OUT 6 MOSFET CONTROL
FET Drives
OUT 3 MOSFET CONTROL
OUT 4 MOSFET CONTROL
OUT 5 MOSFET CONTROL
OUT 1 MOSFET CONTROL
OUT 2 MOSFET CONTROL
Low current output Voltage Select
OUT 0 MOSFET CONTROL
OUT0 - OUT3 - High current MOSFETs
SBC->Duet
Duet->SBC
RPI Comms Buffers
